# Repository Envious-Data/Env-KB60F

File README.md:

# Env-KB60F
 Another Custom Mechanical Keyboard... F stands for FOREHEAD!

 Project Name: KB60F
 Nickname: Lil Delirium

### About!
This is a simple-ish 60% design using a Raspberry Pi Pico. Its a standard 60% layout supporting ANSI and ISO.
Optionally if you have your own PCBs made you can use some pogo pins with a 1mm post to connect the TP pads on the underside of a raspberry pi pico, This will allow functionality of the USB type-c port if populated.

there are some spare GPIOs and a space for a header (mainly for a small oled) so feel free to add things if you can, I always enjoy seeing people using my keyboards for things I never thought of or intended.

### DETAILS
This keyboard has been merged into QMK so you can either compile it from the QMK code or download the pre-built firmware
https://github.com/qmk/qmk_firmware/tree/master/keyboards/enviousdesign/60f

https://github.com/Envious-Data/EnvKB-QMK/tree/main/_PREBUILTFIRMWARES

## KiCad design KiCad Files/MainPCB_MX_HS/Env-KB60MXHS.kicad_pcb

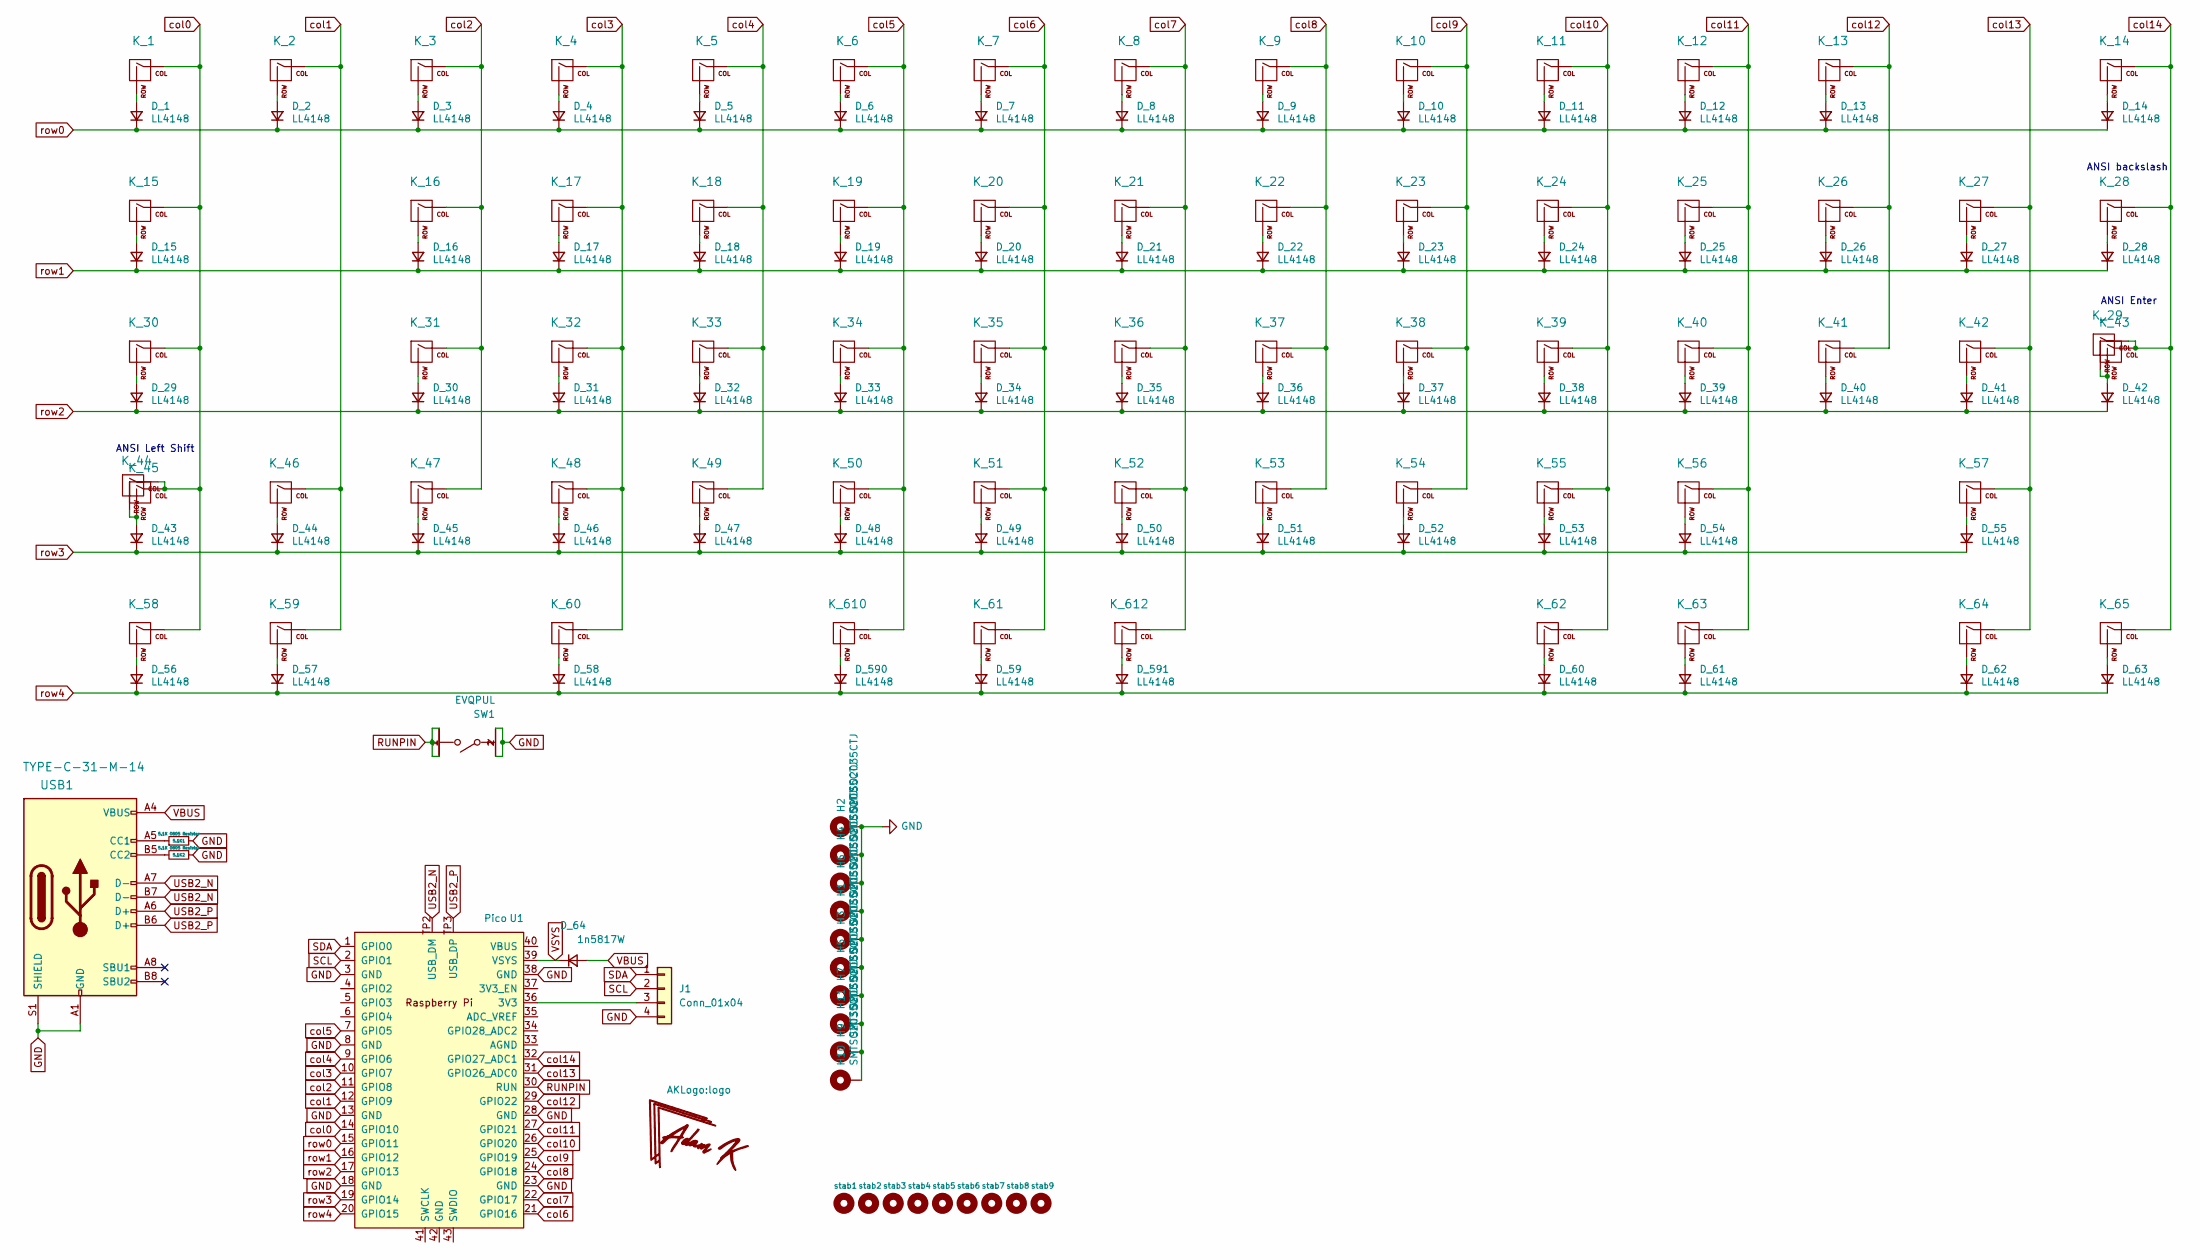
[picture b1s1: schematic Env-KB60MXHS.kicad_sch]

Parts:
5.1K1, 5.1K2: 5.1K 0805 Resistor; R_0805_2012Metric_Pad1.20x1.40mm_HandSolder
D_1, D_2, D_3, D_4, D_5, D_6, D_7, D_8, D_9, D_10, D_11, D_12, D_13, D_14, D_15, D_16, D_17, D_18, D_19, D_20, D_21, D_22, D_23, D_24, D_25, D_26, D_27, D_28, D_29, D_30, D_31, D_32, D_33, D_34, D_35, D_36, D_37, D_38, D_39, D_40, D_41, D_42, D_43, D_44, D_45, D_46, D_47, D_48, D_49, D_50, D_51, D_52, D_53, D_54, D_55, D_56, D_57, D_58, D_59, D_60, D_61, D_62, D_63, D_590, D_591: LL4148; SOD-123+D_DO-35_SOD27_P7.62mm_Horizontal
D_64: 1n5817W; D_SOD-123
H1, H2, H3, H4, H5, H6, H7, H9, H10, H11: SMTSO2035CTJ; MountingHole_2.2mm_M2-MODIFIED
J1: Conn_01x04; PinSocket_1x04_P2.54mm_Vertical
K_1, K_2, K_3, K_4, K_5, K_6, K_7, K_8, K_9, K_10, K_11, K_12, K_13, K_14, K_15, K_16, K_17, K_18, K_19, K_20, K_21, K_22, K_23, K_24, K_25, K_26, K_27, K_28, K_29, K_30, K_31, K_32, K_33, K_34, K_35, K_36, K_37, K_38, K_39, K_40, K_41, K_42, K_43, K_44, K_45, K_46, K_47, K_48, K_49, K_50, K_51, K_52, K_53, K_54, K_55, K_56, K_57, K_58, K_59, K_60, K_61, K_62, K_63, K_64, K_65, K_610, K_612: CPG151101S11; MXOnly-1U-Hotswap-Modified
SW1: EVQPUL; Panasonic_EVQPUL_EVQPUC
U1: Pico; RPi_Pico_SMD_TH_MODIFIED
USB1: TYPE-C-31-M-14; USB_C_TYPE-C-31-M-14; MPN U262-161N-4BVC11; LCSC C319148
stab1, stab2, stab3, stab4, stab5, stab6, stab7, stab8: MX Stabilizer; Stabilizer_Cherry_MX_2u
stab9: MX Stabilizer; Stabilizer_Cherry_MX_6.25u

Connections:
GND: 5.1K1.2, 5.1K2.1, J1.4, SW1.2, SW1.2', U1.3 (GND), U1.8 (GND), U1.13 (GND), U1.18 (GND), U1.23 (GND), U1.28 (GND), U1.38 (GND), USB1.A1 (GND), USB1.A12 (GND), USB1.B1 (GND), USB1.B12 (GND), USB1.S1 (SHIELD)
unnamed: D_1.2 (A), K_1.2 (ROW)
unnamed: D_2.2 (A), K_2.2 (ROW)
unnamed: D_3.2 (A), K_3.2 (ROW)
unnamed: D_4.2 (A), K_4.2 (ROW)
unnamed: D_5.2 (A), K_5.2 (ROW)
unnamed: D_6.2 (A), K_6.2 (ROW)
unnamed: D_7.2 (A), K_7.2 (ROW)
unnamed: D_8.2 (A), K_8.2 (ROW)
unnamed: D_9.2 (A), K_9.2 (ROW)
unnamed: D_10.2 (A), K_10.2 (ROW)
unnamed: D_11.2 (A), K_11.2 (ROW)
unnamed: D_12.2 (A), K_12.2 (ROW)
unnamed: D_13.2 (A), K_13.2 (ROW)
unnamed: D_14.2 (A), K_14.2 (ROW)
unnamed: D_15.2 (A), K_15.2 (ROW)
unnamed: D_16.2 (A), K_16.2 (ROW)
unnamed: D_17.2 (A), K_17.2 (ROW)
unnamed: D_18.2 (A), K_18.2 (ROW)
unnamed: D_19.2 (A), K_19.2 (ROW)
unnamed: D_20.2 (A), K_20.2 (ROW)
unnamed: D_21.2 (A), K_21.2 (ROW)
unnamed: D_22.2 (A), K_22.2 (ROW)
unnamed: D_23.2 (A), K_23.2 (ROW)
unnamed: D_24.2 (A), K_24.2 (ROW)
unnamed: D_25.2 (A), K_25.2 (ROW)
unnamed: D_26.2 (A), K_26.2 (ROW)
unnamed: D_27.2 (A), K_27.2 (ROW)
unnamed: D_28.2 (A), K_28.2 (ROW)
unnamed: D_29.2 (A), K_30.2 (ROW)
unnamed: D_30.2 (A), K_31.2 (ROW)
unnamed: D_31.2 (A), K_32.2 (ROW)
unnamed: D_32.2 (A), K_33.2 (ROW)
unnamed: D_33.2 (A), K_34.2 (ROW)
unnamed: D_34.2 (A), K_35.2 (ROW)
unnamed: D_35.2 (A), K_36.2 (ROW)
unnamed: D_36.2 (A), K_37.2 (ROW)
unnamed: D_37.2 (A), K_38.2 (ROW)
unnamed: D_38.2 (A), K_39.2 (ROW)
unnamed: D_39.2 (A), K_40.2 (ROW)
unnamed: D_40.2 (A), K_41.2 (ROW)
unnamed: D_41.2 (A), K_42.2 (ROW)
unnamed: D_42.2 (A), K_29.2 (ROW), K_43.2 (ROW)
unnamed: D_43.2 (A), K_44.2 (ROW), K_45.2 (ROW)
unnamed: D_44.2 (A), K_46.2 (ROW)
unnamed: D_45.2 (A), K_47.2 (ROW)
unnamed: D_46.2 (A), K_48.2 (ROW)
unnamed: D_47.2 (A), K_49.2 (ROW)
unnamed: D_48.2 (A), K_50.2 (ROW)
unnamed: D_49.2 (A), K_51.2 (ROW)
unnamed: D_50.2 (A), K_52.2 (ROW)
unnamed: D_51.2 (A), K_53.2 (ROW)
unnamed: D_52.2 (A), K_54.2 (ROW)
unnamed: D_53.2 (A), K_55.2 (ROW)
unnamed: D_54.2 (A), K_56.2 (ROW)
unnamed: D_55.2 (A), K_57.2 (ROW)
unnamed: D_56.2 (A), K_58.2 (ROW)
unnamed: D_57.2 (A), K_59.2 (ROW)
unnamed: D_58.2 (A), K_60.2 (ROW)
unnamed: D_59.2 (A), K_61.2 (ROW)
unnamed: D_60.2 (A), K_62.2 (ROW)
unnamed: D_61.2 (A), K_63.2 (ROW)
unnamed: D_62.2 (A), K_64.2 (ROW)
unnamed: D_63.2 (A), K_65.2 (ROW)
unnamed: D_590.2 (A), K_610.2 (ROW)
unnamed: D_591.2 (A), K_612.2 (ROW)
unnamed: H1.1, H2.1, H3.1, H4.1, H5.1, H6.1, H7.1, H9.1, H10.1, H11.1
unnamed: J1.3, U1.36 (3V3)
unnamed: 5.1K1.1, USB1.A5 (CC1)
unnamed: 5.1K2.2, USB1.B5 (CC2)
RUNPIN: SW1.1, SW1.1', U1.30 (RUN)
SCL: J1.2, U1.2 (GPIO1)
SDA: J1.1, U1.1 (GPIO0)
USB2_N: U1.TP2 (USB_DM), USB1.A7 (D-), USB1.B7 (D-)
USB2_P: U1.TP3 (USB_DP), USB1.A6 (D+), USB1.B6 (D+)
VBUS: D_64.2 (A), USB1.A4 (VBUS), USB1.A9 (VBUS), USB1.B4 (VBUS), USB1.B9 (VBUS)
VSYS: D_64.1 (K), U1.39 (VSYS)
col0: K_1.1 (COL), K_15.1 (COL), K_30.1 (COL), K_44.1 (COL), K_45.1 (COL), K_58.1 (COL), U1.14 (GPIO10)
col1: K_2.1 (COL), K_46.1 (COL), K_59.1 (COL), U1.12 (GPIO9)
col2: K_3.1 (COL), K_16.1 (COL), K_31.1 (COL), K_47.1 (COL), U1.11 (GPIO8)
col3: K_4.1 (COL), K_17.1 (COL), K_32.1 (COL), K_48.1 (COL), K_60.1 (COL), U1.10 (GPIO7)
col4: K_5.1 (COL), K_18.1 (COL), K_33.1 (COL), K_49.1 (COL), U1.9 (GPIO6)
col5: K_6.1 (COL), K_19.1 (COL), K_34.1 (COL), K_50.1 (COL), K_610.1 (COL), U1.7 (GPIO5)
col6: K_7.1 (COL), K_20.1 (COL), K_35.1 (COL), K_51.1 (COL), K_61.1 (COL), U1.21 (GPIO16)
col7: K_8.1 (COL), K_21.1 (COL), K_36.1 (COL), K_52.1 (COL), K_612.1 (COL), U1.22 (GPIO17)
col8: K_9.1 (COL), K_22.1 (COL), K_37.1 (COL), K_53.1 (COL), U1.24 (GPIO18)
col9: K_10.1 (COL), K_23.1 (COL), K_38.1 (COL), K_54.1 (COL), U1.25 (GPIO19)
col10: K_11.1 (COL), K_24.1 (COL), K_39.1 (COL), K_55.1 (COL), K_62.1 (COL), U1.26 (GPIO20)
col11: K_12.1 (COL), K_25.1 (COL), K_40.1 (COL), K_56.1 (COL), K_63.1 (COL), U1.27 (GPIO21)
col12: K_13.1 (COL), K_26.1 (COL), K_41.1 (COL), U1.29 (GPIO22)
col13: K_27.1 (COL), K_42.1 (COL), K_57.1 (COL), K_64.1 (COL), U1.31 (GPIO26_ADC0)
col14: K_14.1 (COL), K_28.1 (COL), K_29.1 (COL), K_43.1 (COL), K_65.1 (COL), U1.32 (GPIO27_ADC1)
row0: D_1.1 (K), D_2.1 (K), D_3.1 (K), D_4.1 (K), D_5.1 (K), D_6.1 (K), D_7.1 (K), D_8.1 (K), D_9.1 (K), D_10.1 (K), D_11.1 (K), D_12.1 (K), D_13.1 (K), D_14.1 (K), U1.15 (GPIO11)
row1: D_15.1 (K), D_16.1 (K), D_17.1 (K), D_18.1 (K), D_19.1 (K), D_20.1 (K), D_21.1 (K), D_22.1 (K), D_23.1 (K), D_24.1 (K), D_25.1 (K), D_26.1 (K), D_27.1 (K), D_28.1 (K), U1.16 (GPIO12)
row2: D_29.1 (K), D_30.1 (K), D_31.1 (K), D_32.1 (K), D_33.1 (K), D_34.1 (K), D_35.1 (K), D_36.1 (K), D_37.1 (K), D_38.1 (K), D_39.1 (K), D_40.1 (K), D_41.1 (K), D_42.1 (K), U1.17 (GPIO13)
row3: D_43.1 (K), D_44.1 (K), D_45.1 (K), D_46.1 (K), D_47.1 (K), D_48.1 (K), D_49.1 (K), D_50.1 (K), D_51.1 (K), D_52.1 (K), D_53.1 (K), D_54.1 (K), D_55.1 (K), U1.19 (GPIO14)
row4: D_56.1 (K), D_57.1 (K), D_58.1 (K), D_59.1 (K), D_60.1 (K), D_61.1 (K), D_62.1 (K), D_63.1 (K), D_590.1 (K), D_591.1 (K), U1.20 (GPIO15)

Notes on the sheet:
ANSI Left Shift
ANSI backslash
ANSI Enter

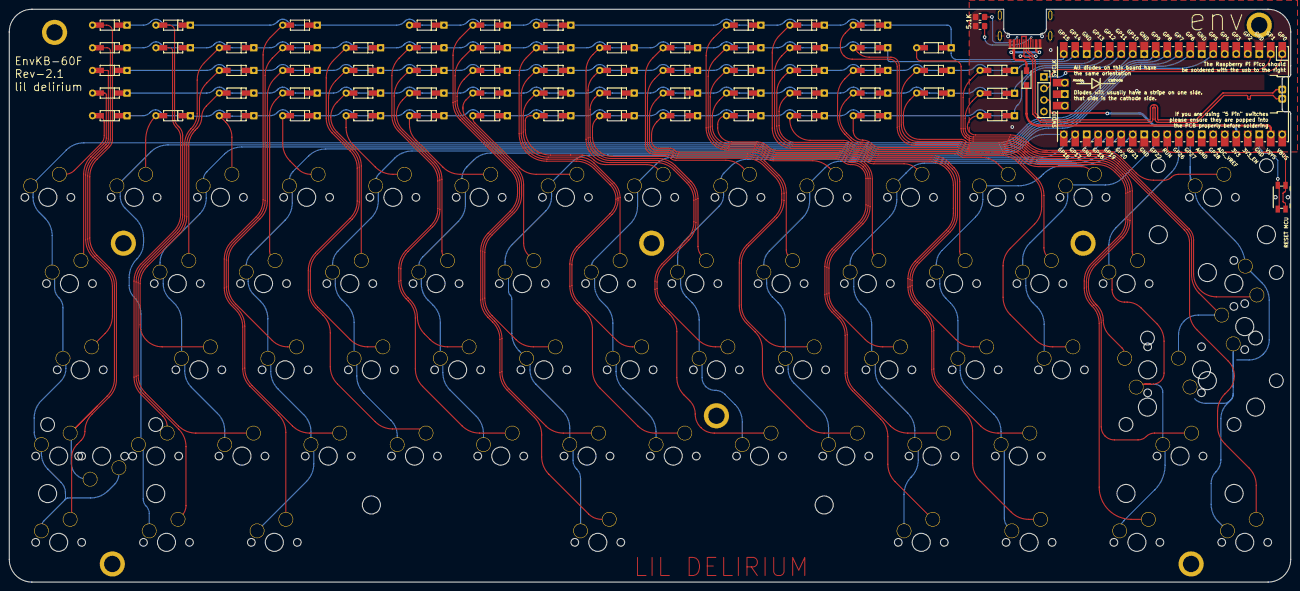
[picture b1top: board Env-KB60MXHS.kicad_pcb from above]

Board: 2 copper layers, 283.0 x 126.5 mm, 151 parts (0 on the bottom side), 94 nets.

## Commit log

2021-04-23 Added Files n whatnot
2021-04-23 Aligned diodes as preferred
2021-04-23 Diodes were wrong direction
2021-04-23 Added More traces n stuff
2021-04-23 General Re-doing of stuff
2021-04-24 Added some mount holes n stuff
2021-04-24 Spotted a lil derp and fixed it
2021-04-24 Added some stuff
    Added a Button for reset and also a bunch of silkscreen instructions for building the keyboard aswell as a QR Code URL that brings you to this Repository.
2021-04-24 Changed QR Code
    meh its a easter egg now.
2021-05-05 Mount hole adjustments
2021-05-06 Added ANSI Left Shift, Enter and Backslash
2021-05-11 Designed New Plate, adjusted mount holes and fixed trace issues.
2021-05-16 Added a optional top USB port based on feedback
2021-05-16 Added missing graphic
2021-05-25 Cleaned up Repo - Adjusted traces and mount hole locations + generated blank back PCB
2021-05-25 Moved MCU lower to allow for mount hole to fit properly, Generated Gerber and bottom plate Gerber
2021-05-27 Corrected silkscreen, Generated updated Gerbers
2021-05-27 somehow missed a screwup on the silkscreen
2021-05-31 General Checkover and adjustments, Generated Gerbers for JLCPCB
2021-06-11 Tweaked USB P/N Traces
2021-06-15 Generated DXF for CNC or Laser cut.
2021-06-29 Added a basic keymap for the keyboard
2021-08-01 Made Laser Cut stuff for top plate
2021-08-04 updated laser cut dxf
2021-08-20 moved a CC resistor out of the way of some silkscreen.
2021-08-21 updated keymap to work with latest kmkfw
2021-08-26 updated keymap to match my keyboard more, also included led toggle on capslock press
2021-08-26 woops, fixed capslock not actually toggling.
2021-08-30 fixed backplate's ground fill and added a center logo on the rear of it.
2021-08-30 reorganize folder/files, added triple spacebar
2021-08-30 started work on RP2040 version.
2021-08-30 finished up RP2040 version, need to fill the blank space.
2021-08-30 finished up RP2040 version some more, added debug header and spare GPIO header.
2021-08-30 Corrected mount hole placement on all PCBs and updated the switch plate to fit triple spacebar split.
2021-08-30 updated git ignore to allow BOM/CPL and updated readme.
2021-09-04 tested some logos and placements to fill empty space, might relocate the MCU setup a bit.
2021-09-20 started work on hotswap version
2021-09-20 finished up hotswap version traces
2021-12-01 uploaded QMK uf2, via doesnt work.
2022-05-06 polished up design and removed other versions for now, will re-do hotswap version.
2022-05-06 forgot to save schematic changes
2022-05-06 overall cleanup, will need to fix stuff probably.
2022-05-06 some more updates n stuff
2022-05-06 more cleanup and sorting
2022-05-06 Ran DRC and corrected any errors
2022-05-06 Re-created switchplate
2022-05-06 updated backplate
2022-05-06 updated switch plate
2022-05-18 small tweaks regarding silkscreen
2022-05-18 Created Choc V2 Version
2022-05-18 Generated Choc Plate.
2022-05-19 modified diode footprint so you can fit SMD diodes, added hole for USB castellation. probably much more that I forgot as usual.
2022-05-20 renamed choc V2 version project
2022-05-20 gitignore updates
2022-05-30 swapped power input for MCU to VSYS instead of VBUS
2022-06-07 updated gitignore
2022-06-16 some various corrections to the USB DP/DM traces
2022-06-24 swapped mount holes
2022-06-26 redid front traces to be less mechanically damage prone
2022-06-27 re-done traces on choc v2 version
2022-07-21 some work for making CAD work a bit easier for future use
2022-07-23 added updated circuitpython firmware for those who are still prefer it
2022-07-25 starting initial cleanup
2022-07-25 moved mount hole, redid switchplate and backplate
2022-10-06 made some temporary adjustments to test SMD Nuts
2022-10-07 some checking over for future
2022-10-12 added I2C header and protection diode to MX version
2022-10-12 made hotswap version based on MX variant
2022-10-12 rounded the tracks and all that, prepare for order via Gerber generation
2022-11-19 modified main version to fit smd nuts and also solderable shims
2022-12-01 modified mount holes for future test
2023-01-09 adjusted designs and generated gerbers
2023-02-02 added split backspace and right shift
    backspace is 1u+1u and right shift is 1.75u + 1u.
2023-02-07 generated some gerbers among other tweaks
2023-05-03 corrected issue on MX variant, spacebar was not aligned correctly
2023-09-27 updated MX version a tiny bit, might order and do a tiny kit run.
2023-09-29 various design work toward producing and making a case
2023-12-08 Made experiment version and some experimental diode footprint.
2023-12-08 got rid of experimental version as it served its purpose.
2023-12-08 updated Gerber
2023-12-08 update readme and image on readme
2023-12-08 Corrected mount hole parity between mainPCB MX and Backplate.
2023-12-08 got rid of choc versions as they are non viable sadly.
2023-12-08 fixed parity between main MX PCB and switch plate.
2023-12-08 made extended outline versions
2023-12-08 Decided extended plates are the norm.
2023-12-08 re-made a couple files I forgot to include.
2023-12-11 corrected font.
2024-01-27 updated hotswap version to have SMT compatible diode footprints
2024-01-27 generated gerbers
2024-01-31 updated logos
2024-04-23 corrected an issue
2024-08-27 fixed issues with alignment
2024-09-19 fixed alignment issues, generated gerbers, fixed silkscreen issues, fixed footprints, generated gerbers
2024-09-19 updated BOM,CPL to include missing parts needed, updated the values
2024-10-16 Corrected Several issues pointed out by Dasky (tyvm), reduced top cover size to not conflict with the plate, swapped oled header power for correct voltage, extended several pads to make it easier to 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
2024-10-16 fixed a missing ground connection.
2024-10-17 changed TP pad cutout for USB to be on the edge of the board for easier soldering, updated silkscreen note.
2024-10-17 forgot to save and commit changes on the PCB file.
2024-10-18 fixed iso enter stabiliser position, validated position of ansi enter, ansi backslash, iso enter, iso right bracket, iso hash key.
2024-11-26 generated pcb image and uploaded to imgur
2025-03-02 removed ground fill to see how it would look with transparent soldermask
